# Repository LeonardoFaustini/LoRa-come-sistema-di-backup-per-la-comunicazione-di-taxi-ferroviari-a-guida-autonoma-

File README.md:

# Guida alla repository GitHub

In questa sezione è riportata una breve guida a questa repository GitHub, la quale contiene tutto il materiale relativo al lavoro svolto nel tiroinio e nella tesi, tra cui i codici sorgente, i file STL, l'analisi delle antenne tramite nanoVNA e i risultati della parte di test. 

L'organizzazione delle cartelle del progetto è spiegata qui di seguito:

### Firmware
Nella cartella `File_di_configurazione_ESP32-LoRa` sono stati inseriti i firmware dei moduli trasmettitore e ricevitori usati per le topologie P2P e Star.

### Risultati test
In questa cartella sono stati inseriti tutti i dati acquisiti nelle fasi di test. Essi sono suddivisi in base alla topologia e alla configurazione usata, in base alla frequenza, duty cycle e potenza di trasmissione. All'interno di ogni configurazione sono presenti i relativi file csv ottenuti da seriale e da ThingSpeak e i relativi grafici (RSSI-distanza, SNR-distanza, RSSI-SNR, distribuzione dell’RSSI e una mappa interattiva che rappresenta i diversi pacchetti ricevuti mostrandone ID, distanza dal ricevitore e relativo RSSI).

### Case prototipo 3D
All'interno di questa cartella sono inseriti i file STL del case del prototipo e dell'antenna creata, già orientati e settati correttamente per la stampa FDM.

### Codici Python, lettura seriale e grafici
In questa cartella è presente il codice Python usato per leggere e salvare i dati dalla seriale in fase di test e un notebook usato per passare dai dati csv ai grafici.

Inoltre, la repository contiene l'analisi tramite VNA delle diverse antenne usate in fase di test, lo schematico KiCad per il collegamento tra il modulo GPS e la Heltec, i codici MATLAB usati su ThingSpeak per spacchettare i buffer di dati ricevuti per poterne plottare i grafici.

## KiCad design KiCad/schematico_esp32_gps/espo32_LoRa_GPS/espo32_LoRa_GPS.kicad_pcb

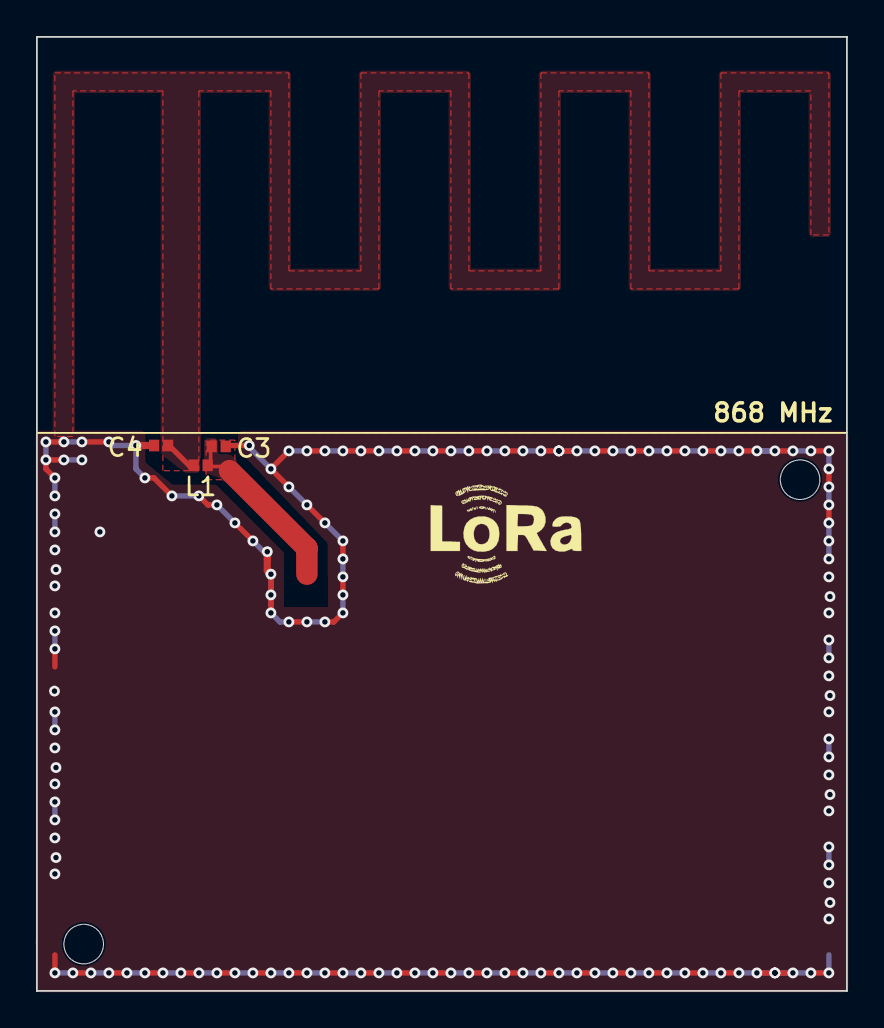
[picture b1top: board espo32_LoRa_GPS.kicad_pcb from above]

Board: 2 copper layers, 45.0 x 53.0 mm, 5 parts (0 on the bottom side), 2 nets.

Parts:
C3, C4: dnp; C_0402_1005Metric
J7, J8: Conn_01x01; MountingHole_2.2mm_M2
L1: 0R; L_0402_1005Metric

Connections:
GND: C3.2, C4.1, C4.2, L1.2
unnamed: C3.1, L1.1

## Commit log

2026-05-27 Update README with additional information
    Added a new section outlining attached materials.
2026-05-27 Add files via upload
    In questa cartella sono riportati i paper sui quali si è fondata la base teorica di LoRa.
2026-05-27 Revert "Add files via upload"
2026-06-05 Add file via terminal
2026-06-05 Create README.md with project description
    Add initial README with project description.
2026-06-27 Refine README content for clarity and detail
    Updated descriptions for test results, 3D case files, Python codes, and additional content.
2026-06-27 Update README to remove extraneous content
    Removed references to papers, articles, and datasheets from the README.
